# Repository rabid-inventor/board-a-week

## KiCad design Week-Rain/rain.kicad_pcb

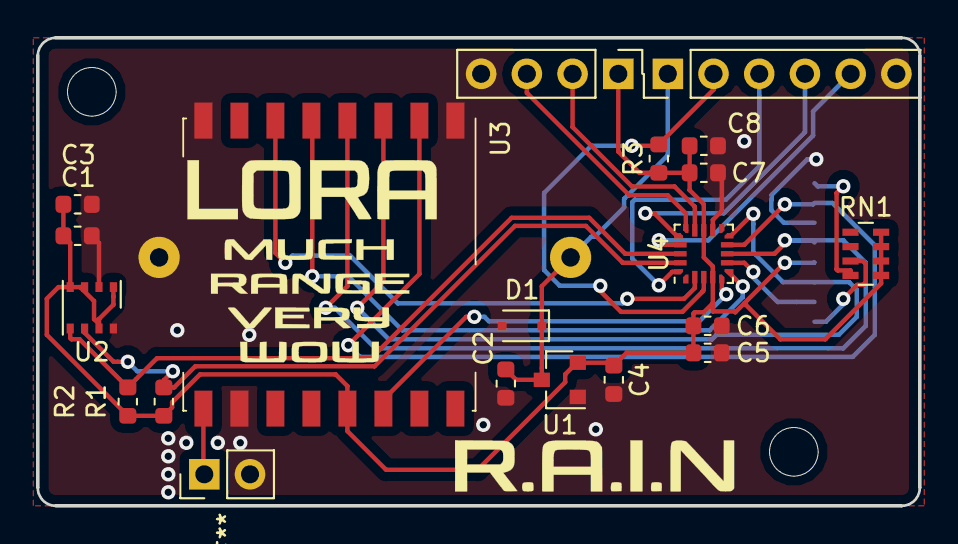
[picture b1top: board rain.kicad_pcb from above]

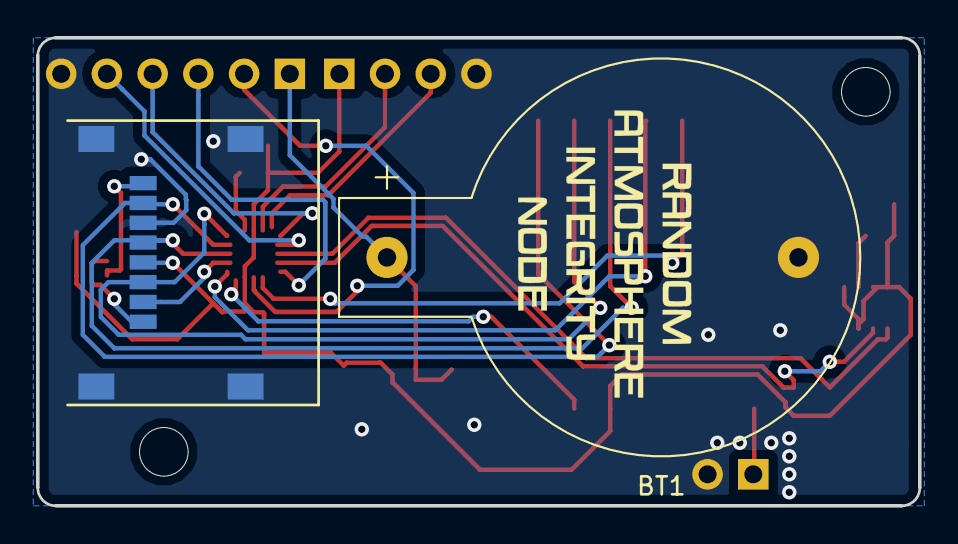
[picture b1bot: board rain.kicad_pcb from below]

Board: 2 copper layers, 49.0 x 26.0 mm, 21 parts (2 on the bottom side), 20 nets.

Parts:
BT1: Battery_Cell; CR2032H
C1, C5, C7: 1uF; C_0603_1608Metric
C2, C4: C_Small; C_0603_1608Metric
C3: 100uF; C_0603_1608Metric
C6, C8: 100nF; C_0603_1608Metric
D1: D; D_SOD-323F
J1: Conn_01x06_Female; PinHeader_1x06_P2.54mm_Vertical
J2: Micro_SD_Card_Det; MicroSd_Wurth_693072010801
J3: Conn_01x04_Female; PinHeader_1x04_P2.54mm_Vertical
R1, R2: 4k7; R_0603_1608Metric
R3: 10k; R_0603_1608Metric
RN1: R_Pack04; R_Array_Concave_4x0603
U1: AP7333-28SRG-7; SOT-23
U2: BME680; Bosch_LGA-8_3x3mm_P0.8mm_ClockwisePinNumbering
U3: RFM95W-868S2; HOPERF_RFM9XW_SMD
U4: STM32L011F4Ux; ST_UFQFPN-20_3x3mm_P0.5mm

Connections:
+VDC: BT1.1, C2.1, D1.1, J1.1, U1.3
/BOOT0: J1.3, U4.20
/I2C1_SCL: R2.2, U2.4, U4.18
/I2C1_SDA: R1.2, U2.3, U4.19
/LORA_INT1: U3.14, U4.5
/LORA_RESET: U3.6, U4.2
/LORA_SS: U3.5, U4.6
/MCU_RESET: J1.2, R3.2, U4.3
/SD_DAT1: J2.8, RN1.4
/SD_DAT2: J2.1, RN1.3
/SPI1_MISO: J2.7, U3.2, U4.9
/SPI1_MOSI: J2.3, U3.3, U4.10
/SPI1_SCK: J2.5, U3.4, U4.8
/SPI1_SS: J2.2, U4.7
/SWCLK: J1.5, U4.17
/SWDIO: J1.4, U4.16
/UART2_RX: J3.3, U4.15
/UART2_TX: J3.2, U4.14
GND: BT1.2, C1.2, C2.2, C3.2, C4.2, C5.2, C6.2, C7.2, C8.2, D1.2, J1.6, J2.6, J2.9, J3.4, U1.1, U2.1, U2.7, U3.1, U3.8, U3.10, U4.12
VDD: C1.1, C3.1, C4.1, C5.1, C6.1, C7.1, C8.1, J2.4, J3.1, R1.1, R2.1, R3.1, RN1.5, RN1.6, RN1.7, RN1.8, U1.2, U2.2, U2.5, U2.6, U2.8, U3.13, U4.4, U4.13

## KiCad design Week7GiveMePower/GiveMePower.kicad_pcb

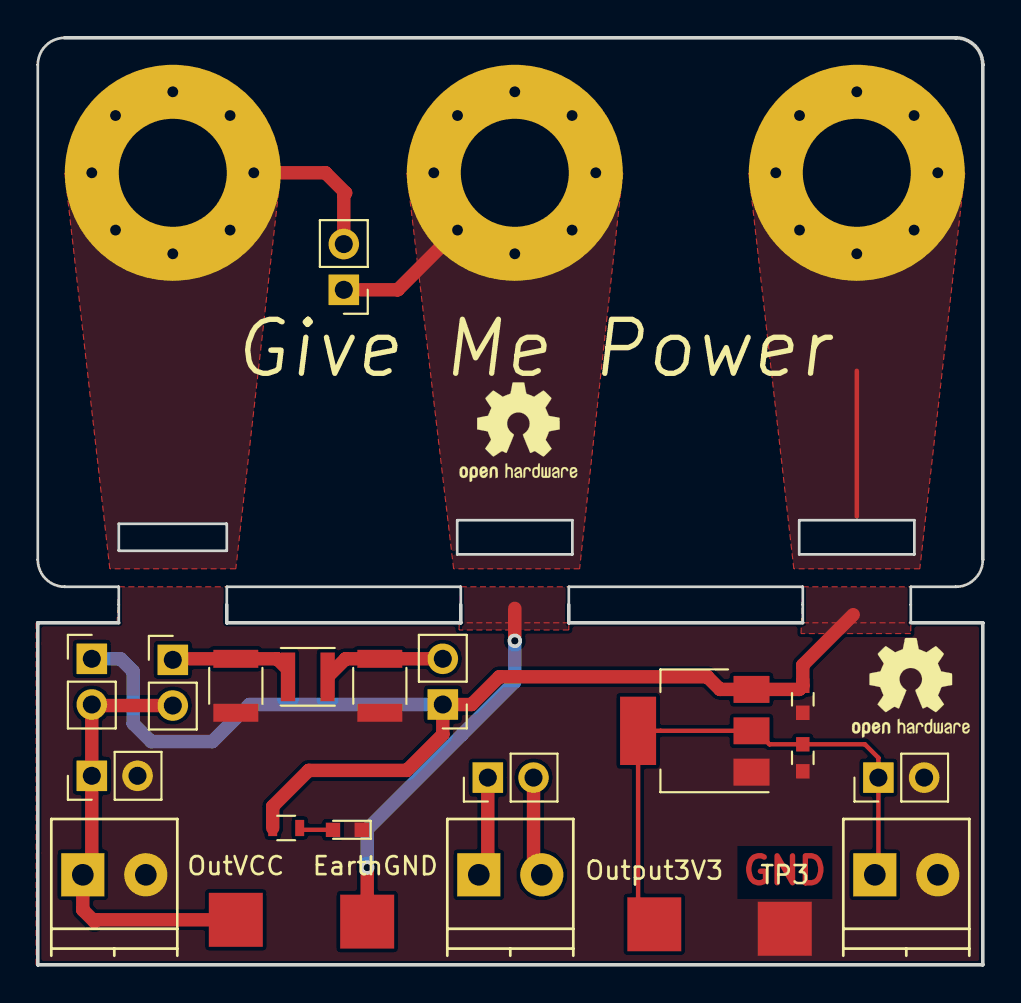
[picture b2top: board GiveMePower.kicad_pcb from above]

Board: 2 copper layers, 52.5 x 51.5 mm, 25 parts (0 on the bottom side), 10 nets.

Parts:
C1, C4: C; C_0603
C2, C3: C; C_1210
D1: LED; LED_0603
EarthGND: Measurement_Point_Square-SMD-Pad_Big
J1, J2, J3, J4: Conn_01x02_Male; Pin_Header_Straight_1x02_Pitch2.54mm
J5, J6, J7: Conn_01x02_Female; Pin_Header_Straight_1x02_Pitch2.54mm
J8, J9, J10: Screw_Terminal_01x02; TerminalBlock_Phoenix_PT-3.5mm_2pol
J11, J12, J13: Conn_01x01_Female; MountingHole_6mm_Pad_Via
L2: L; L_Taiyo-Yuden_MD-3030
OutVCC: TestPoint_Probe; Measurement_Point_Square-SMD-Pad_Big
Output3V3: TestPoint_Probe; Measurement_Point_Square-SMD-Pad_Big
R1: R; R_0603
TP3: TestPoint_Probe; Measurement_Point_Square-SMD-Pad_Big
U1: AP1117-33; SOT-223-3_TabPin2

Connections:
/AUXIn: J7.1, J10.1
/AUXout: J7.2, J10.2
/EarthGND: EarthGND.1, J1.1, J12.1
/LowPassIn: C3.1, J2.2, L2.1
/LowPassOut: C2.1, J4.1, L2.2
/Output3V3: C4.1, J6.1, J9.1, Output3V3.1, U1.2
/OutputVCC: J3.2, J4.2, J5.1, J8.1, OutVCC.1
GND: C1.2, C2.2, C3.2, C4.2, D1.1, J1.2, J5.2, J6.2, J8.2, J9.2, J13.1, TP3.1, U1.1
unnamed: D1.2, R1.2
VCC: C1.1, J2.1, J3.1, J11.1, R1.1, U1.3

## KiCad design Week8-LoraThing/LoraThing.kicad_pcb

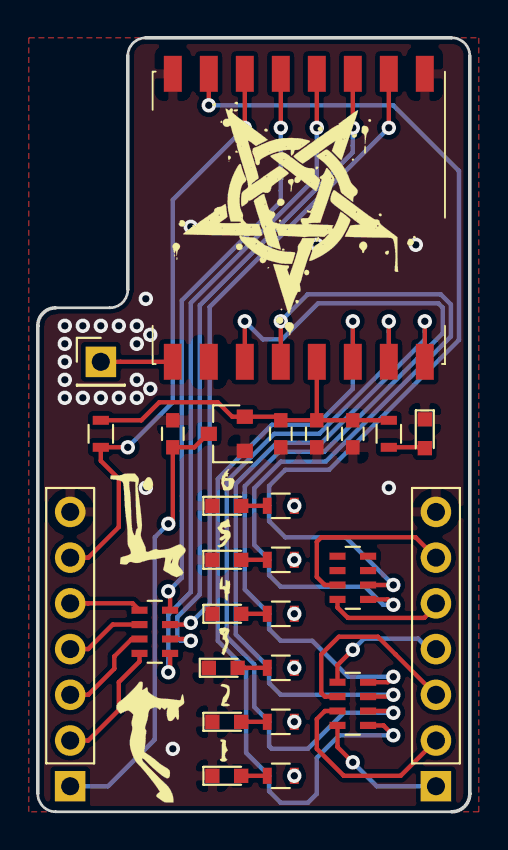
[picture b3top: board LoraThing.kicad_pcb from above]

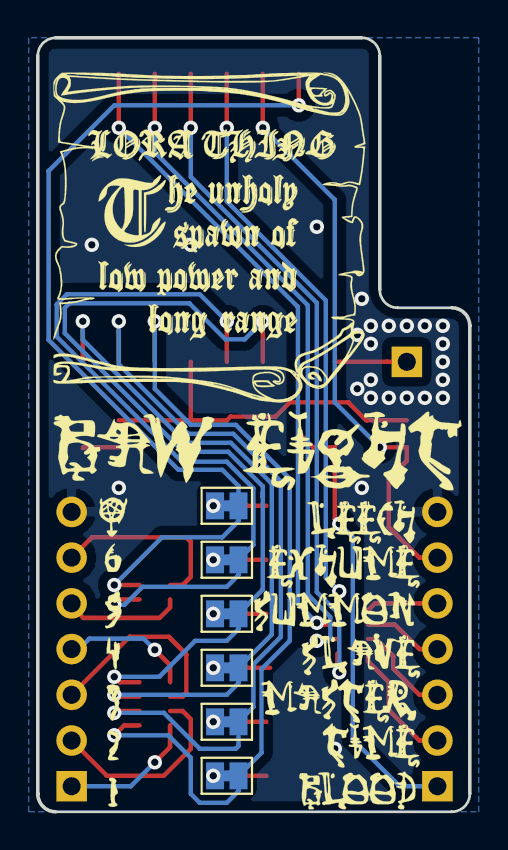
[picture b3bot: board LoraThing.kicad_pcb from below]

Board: 2 copper layers, 24.0 x 43.0 mm, 33 parts (6 on the bottom side), 38 nets.

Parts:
C1, C2, C4: 1uF; C_0603
C3: 100nF; C_0603
D1, D2, D3, D4, D5, D6, D7: LED; LED_0603
J1, J2: Conn_01x07_Male; Pin_Header_Straight_1x07_Pitch2.54mm
J3: Conn_01x01_Female; Pin_Header_Straight_1x01_Pitch2.54mm
JP1, JP2, JP4, JP5, JP6: Jumper_NC_Small; SolderJumper-2_P1.3mm_Bridged_Pad1.0x1.5mm
R1, R2, R3, R4, R5, R6, R7: 330R; R_0603
R8: 10K; R_0603
RN1, RN2, RN3: 100R; R_Array_Concave_4x0603
U1: AP7333-33SRG-7; SOT-23
U2: RFM95W-868S2; Hopref_RFM9XW_SMD
eJP3: Jumper_NC_Small; SolderJumper-2_P1.3mm_Bridged_Pad1.0x1.5mm

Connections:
+3V3: C2.1, C3.1, C4.1, R7.2, R8.2, U1.2, U2.13
/ANTENNA: J3.1, U2.9
/EXT_GPIO1: J2.1, RN2.8
/EXT_GPIO2: J2.2, RN2.7
/EXT_GPIO3: J2.3, RN2.6
/EXT_GPIO4: J2.4, RN2.5
/EXT_GPIO5: J2.5, RN3.8
/EXT_GPIO6: J2.6, RN3.7
/GPIO1: JP1.1, RN2.1, U2.14
/GPIO2: JP2.1, RN2.2, U2.15
/GPIO3: RN2.3, U2.16, eJP3.1
/GPIO4: JP4.1, RN2.4, U2.11
/GPIO5: JP5.1, RN3.1, U2.12
/GPIO6: JP6.1, RN3.2, U2.7
/RESET: J1.6, R8.1, U2.6
/SPI_CS: RN1.4, U2.5
/SPI_EXT_CS: J1.5, RN1.5
/SPI_EXT_MISO: J1.4, RN1.6
/SPI_EXT_MOSI: J1.3, RN1.7
/SPI_EXT_SCK: J1.2, RN1.8
/SPI_MISO: RN1.3, U2.2
/SPI_MOSI: RN1.2, U2.3
/SPI_SCK: RN1.1, U2.4
GND: C1.2, C2.2, C3.2, C4.2, D1.1, D2.1, D3.1, D4.1, D5.1, D6.1, D7.1, J1.7, J2.7, U1.1, U2.1, U2.8, U2.10
unnamed: D1.2, R1.1
unnamed: D2.2, R2.1
unnamed: D3.2, R3.1
unnamed: D4.2, R4.1
unnamed: D5.2, R5.1
unnamed: D6.2, R6.1
unnamed: D7.2, R7.1
unnamed: JP1.2, R1.2
unnamed: JP2.2, R2.2
unnamed: R3.2, eJP3.2
unnamed: JP4.2, R4.2
unnamed: JP5.2, R5.2
unnamed: JP6.2, R6.2
VCC: C1.1, J1.1, U1.3

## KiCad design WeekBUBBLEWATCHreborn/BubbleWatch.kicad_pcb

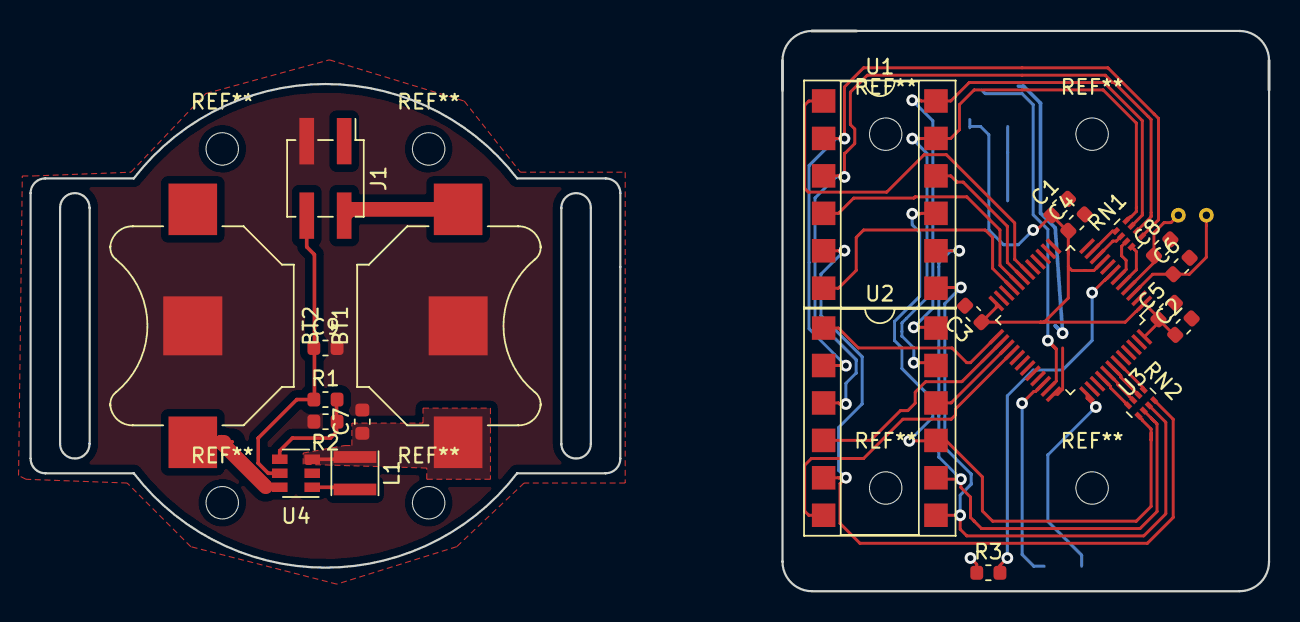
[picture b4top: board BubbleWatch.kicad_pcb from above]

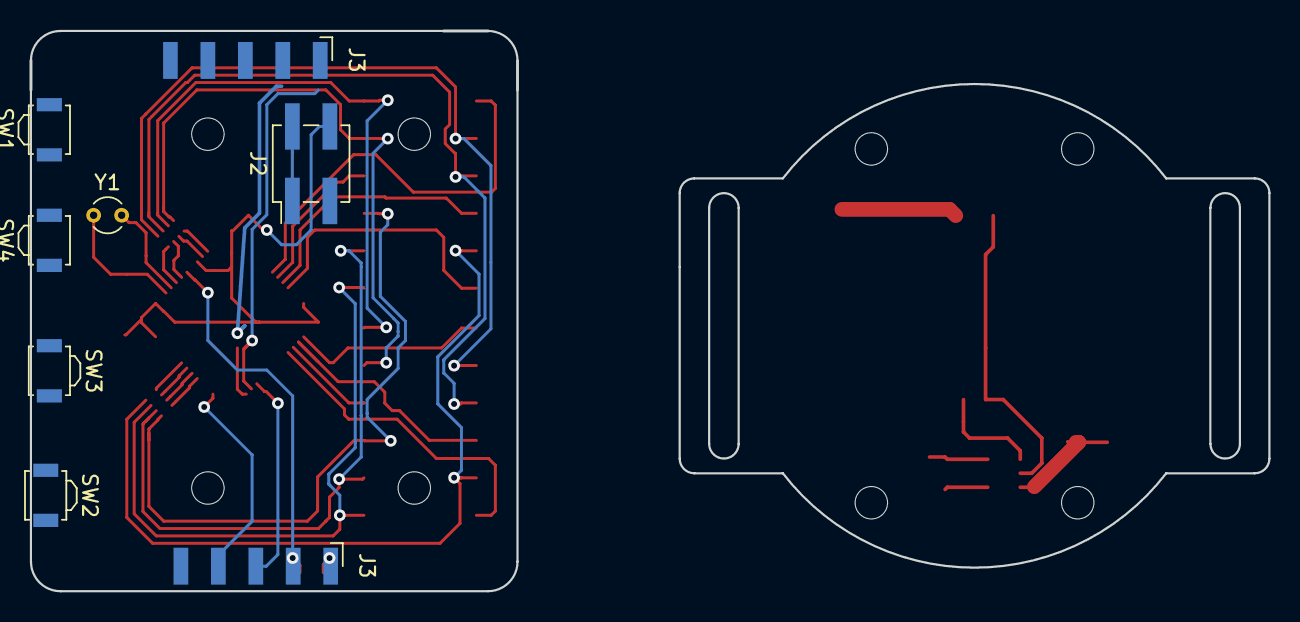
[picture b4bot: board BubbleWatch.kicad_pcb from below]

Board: 2 copper layers, 84.0 x 38.0 mm, 30 parts (8 on the bottom side), 39 nets.

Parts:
BT1, BT2: Battery_Cell; BatteryHolder_Keystone_3000_1x12mm
C1, C7: 4.7uF; C_0603_1608Metric
C2, C3: 100nF; C_0603_1608Metric
C4: 10nF; C_0603_1608Metric
C5: 1uF; C_0603_1608Metric
C6, C8: 12pF; C_0603_1608Metric
C9: 10uF; C_0603_1608Metric
J1, J2: Conn_02x02_Counter_Clockwise; PinHeader_2x02_P2.54mm_Vertical_SMD
J3, J3#2: Conn_01x05; Harwin_M20-89005xx_1x05_P2.54mm_Horizontal
L1: 4.7uH; L_Taiyo-Yuden_NR-30xx
R1: 330K; R_0603_1608Metric
R2: 200k; R_0603_1608Metric
R3: 10k; R_0603_1608Metric
RN1, RN2: 220R; R_Array_Concave_4x0402
SW1, SW2, SW3, SW4: SW_Push; SW_SPST_B3U-3000P
U1, U2: RedRetroBubbleDisplay; DIP-12_W7.62mm_SMDSocket_SmallPads
U3: STM32F030C8Tx; LQFP-48_7x7mm_P0.5mm
U4: MCP1640BCH; SOT-23-6
Y1: Crystal; Crystal_C26-LF_D2.1mm_L6.5mm_Vertical

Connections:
+3V3: C1.1, C2.1, C3.1, C4.1, C5.1, C9.1, J1.4, J2.4, J3.1, J3#2.1, R1.1, R3.1, U3.1, U3.9, U3.24, U3.48, U4.5
+BATT: BT1.1, BT2.1, C7.1, J1.1, J1.2, J2.1, J2.2, L1.1, U4.3, U4.6
/BUTTON1: SW1.2, U3.12
/BUTTON2: SW2.2, U3.13
/BUTTON3: SW3.2, U3.14
/BUTTON4: SW4.2, U3.15
/DIS1: U1.1, U3.18
/DIS2: U1.10, U3.19
/DIS3: U1.4, U3.20
/DIS4: U1.6, U3.21
/DIS5: U2.1, U3.25
/DIS6: U2.10, U3.27
/DIS7: U2.4, U3.26
/DIS8: U2.6, U3.28
/IOSEGA: RN1.4, U3.5
/IOSEGB: RN1.3, U3.6
/IOSEGC: RN1.2, U3.10
/IOSEGD: RN1.1, U3.11
/IOSEGDP: RN2.1, U3.43
/IOSEGE: RN2.4, U3.40
/IOSEGF: RN2.3, U3.41
/IOSEGG: RN2.2, U3.42
/RESET: J3.2, J3#2.2, R3.2, U3.7
/RTC_XTAL_IN: C6.1, U3.3, Y1.1
/RTC_XTAL_OUT: C8.1, U3.4, Y1.2
/SEGA: RN1.7, U1.12, U2.12
/SEGB: RN1.8, U1.11, U2.11
/SEGC: RN1.6, U1.3, U2.3
/SEGD: RN2.6, U1.8, U2.8
/SEGDP: RN2.8, U1.5, U2.5
/SEGE: RN1.5, U1.2, U2.2
/SEGF: RN2.5, U1.9, U2.9
/SEGG: RN2.7, U1.7, U2.7
/SWDCLK: J3.4, J3#2.4, U3.37
/SWDIO: J3.3, J3#2.3, U3.34
GND: BT1.2, BT2.2, C1.2, C2.2, C3.2, C4.2, C5.2, C6.2, C7.2, C8.2, C9.2, J1.3, J2.3, J3.5, J3#2.5, R2.2, U3.8, U3.23, U3.47, U4.2
unnamed: L1.2, U4.1
unnamed: R1.2, R2.1, U4.4
unnamed: SW1.1, SW2.1, SW3.1, SW4.1
